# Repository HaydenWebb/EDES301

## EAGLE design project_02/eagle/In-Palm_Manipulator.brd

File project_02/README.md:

# In-Palm 2DoF Manipulator PCB
Implementation files (gerber, schematic, BOM, etc.) for generating a PCB for the manipulator

## Project Description
In-the-palm 2DoF manipulator that will be worn on both the forearm and hand. This device will be comprised of an active surface (i.e. a pulley belt) and turntable that will be actuated by two micro DC motors. The control of this device will be actuated by four pressure sensors that will be inlaid along the wrist to measure the bend of the wrist. Depending on the bend of the wrist, either the turntable or active surface will turn on and move.

## PCB Description
The components for this board is a PocketBeagle, L293D, and MT3608. They are connected together through a 4-layer, copper board and has 5mm mounting brackets inset in the corners.

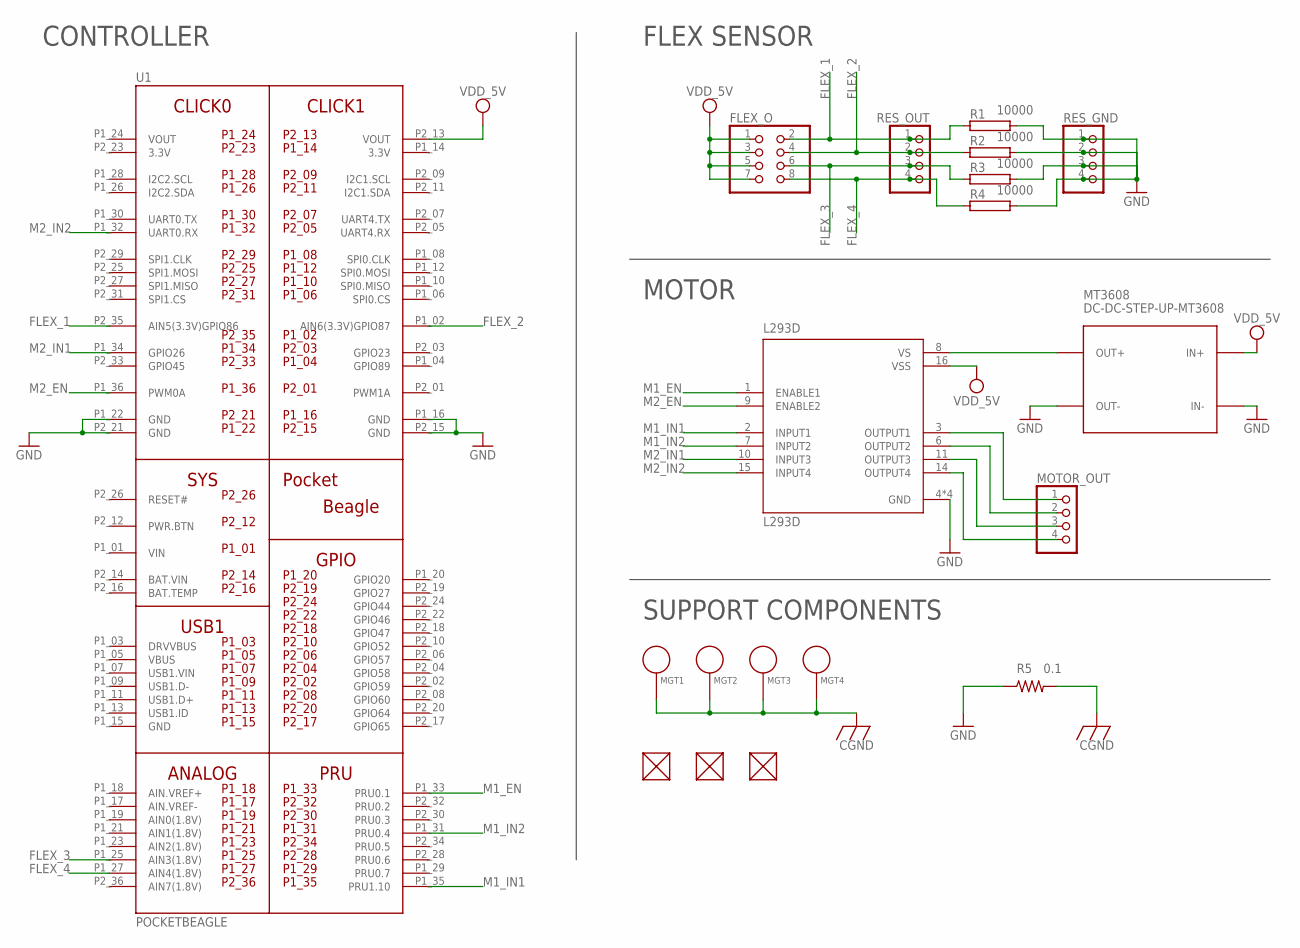
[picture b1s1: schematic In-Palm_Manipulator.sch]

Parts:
FLEX_O: PINHD-2X4; 2X04
FUD1, FUD2, FUD3: FIDUCIAL; FIDUCIAL_40MIL
L293D: L293D; DIP880W50P254L2000H510Q16
MGT1, MGT2, MGT3, MGT4: MOUNTING_HOLE
MOTOR_OUT: PINHD-1X4; 1X04
MT3608: DC-DC-STEP-UP-MT3608
R1, R2, R3, R4: 10000; HPS58
R5: 0.1; R0603
RES_GND: PINHD-1X4; 1X04
RES_OUT: PINHD-1X4; 1X04
U1: POCKETBEAGLE

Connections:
3.3V: U1.P1_14 (3.3V), U1.P2_23 (3.3V)
BAT.VIN: U1.P2_14 (BAT.VIN)
CGND: MGT1.P$1, MGT2.P$1, MGT3.P$1, MGT4.P$1, R5.2
FLEX_1: FLEX_O.2, R1.1, RES_OUT.1, U1.P2_35 (AIN5(3.3V)GPIO86)
FLEX_2: FLEX_O.4, R2.1, RES_OUT.2, U1.P1_02 (AIN6(3.3V)GPIO87)
FLEX_3: FLEX_O.6, R3.1, RES_OUT.3, U1.P1_25 (AIN3(1.8V))
FLEX_4: FLEX_O.8, R4.1, RES_OUT.4, U1.P1_27 (AIN4(1.8V))
GND: L293D.4 (GND), L293D.5 (GND), L293D.12 (GND), L293D.13 (GND), MT3608.IN-, MT3608.OUT-, R1.2, R2.2, R3.2, R4.2, R5.1, RES_GND.1, RES_GND.2, RES_GND.3, RES_GND.4, U1.P1_16 (GND), U1.P1_22 (GND), U1.P2_15 (GND), U1.P2_21 (GND)
M1_EN: L293D.1 (ENABLE1), U1.P1_33 (PRU0.1)
M1_IN1: L293D.2 (INPUT1), U1.P1_35 (PRU1.10)
M1_IN2: L293D.7 (INPUT2), U1.P1_31 (PRU0.4)
M2_EN: L293D.9 (ENABLE2), U1.P1_36 (PWM0A)
M2_IN1: L293D.10 (INPUT3), U1.P1_34 (GPIO26)
M2_IN2: L293D.15 (INPUT4), U1.P1_32 (UART0.RX)
unnamed: L293D.8 (VS), MT3608.OUT+
unnamed: L293D.3 (OUTPUT1), MOTOR_OUT.1
unnamed: L293D.6 (OUTPUT2), MOTOR_OUT.2
unnamed: L293D.11 (OUTPUT3), MOTOR_OUT.3
unnamed: L293D.14 (OUTPUT4), MOTOR_OUT.4
VDD_5V: FLEX_O.1, FLEX_O.3, FLEX_O.5, FLEX_O.7, L293D.16 (VSS), MT3608.IN+, U1.P2_13 (VOUT)
VIN: U1.P1_01 (VIN)
VOUT: U1.P1_24 (VOUT)

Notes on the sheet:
FLEX SENSOR
MOTOR
CONTROLLER
SUPPORT COMPONENTS

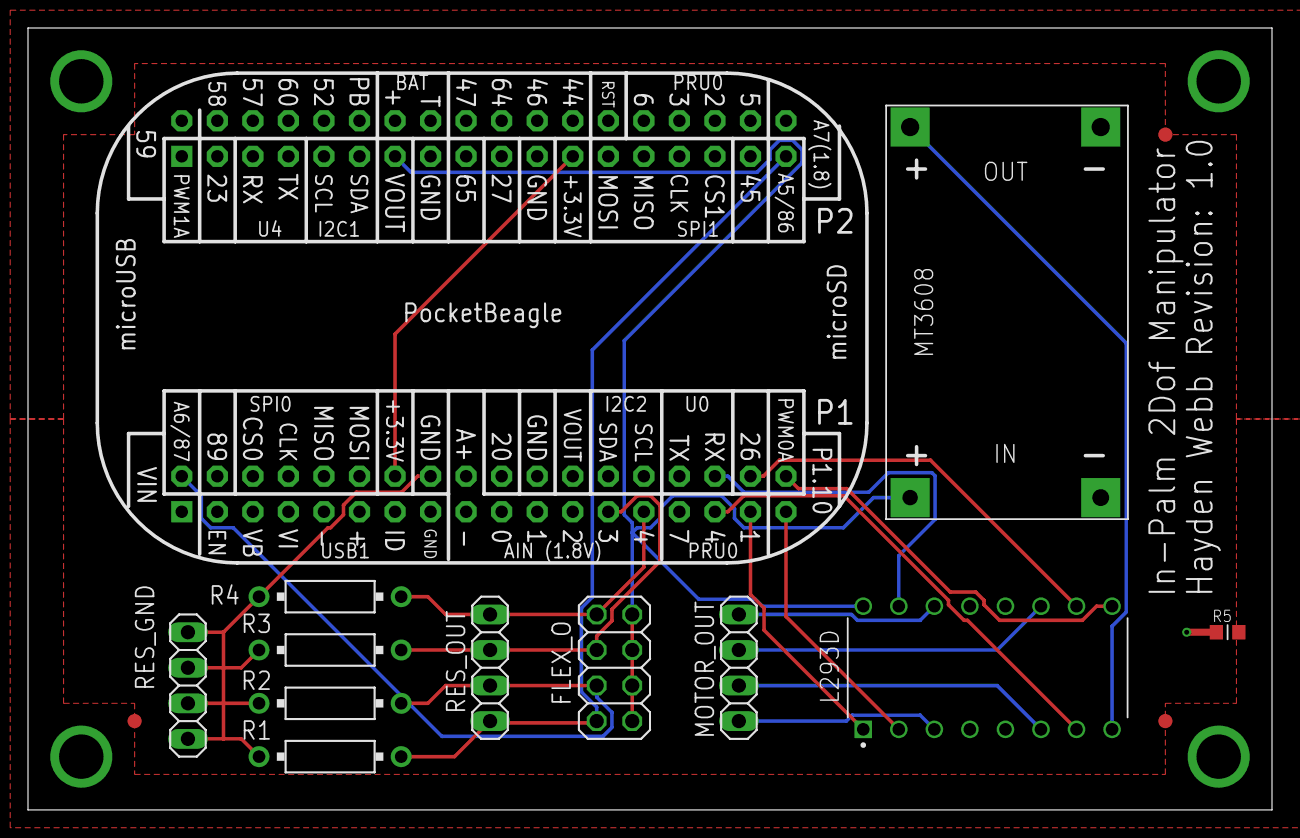
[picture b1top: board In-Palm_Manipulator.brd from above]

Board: 4 copper layers, 88.9 x 55.9 mm, 19 parts (0 on the bottom side), 19 nets.

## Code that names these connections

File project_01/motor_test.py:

#!/usr/bin/env python3
import os
import time
import Adafruit_BBIO.GPIO as GPIO
import Adafruit_BBIO.PWM  as PWM

M2_EN,  M2_IN1,  M2_IN2 = "P1_33", "P1_35", "P1_31"
M1_EN,  M1_IN1,  M1_IN2 = "P1_36", "P1_34", "P1_32"

os.system(f"config-pin {M1_EN} pwm")
os.system(f"config-pin {M2_EN} pwm")
for pin in (M1_IN1, M1_IN2, M2_IN1, M2_IN2):
    os.system(f"config-pin {pin} gpio")
    GPIO.setup(pin, GPIO.OUT)

PWM.start(M1_EN, 0, 1000)   # 1 kHz, 0% duty (off)
PWM.start(M2_EN, 0, 1000)

def motor_on(en, in1, in2, speed_pct=100):
    """Run motor in CW or CCW at speed_pct%."""
    GPIO.output(in1, GPIO.HIGH)
    GPIO.output(in2, GPIO.LOW)
    PWM.set_duty_cycle(en, speed_pct)


def motor_off(en, in1, in2, coast=True):
    """Stop motor; if coast=False, actively brake."""
    PWM.set_duty_cycle(en, 0)
    if not coast:
        # active brake: tie both inputs together
        GPIO.output(in1, GPIO.HIGH)
        GPIO.output(in2, GPIO.HIGH)

if __name__ == "__main__":
    print("Starting alternating motor test (Ctrl-C to quit)...")
    try:
        while True:
            print("→ MOTOR 1 ON")
            try:
                motor_on(M1_EN, M1_IN1, M1_IN2)
            except Exception as e:
                print("Error in motor_on(M1):", repr(e))
            time.sleep(2.0)

            print("→ MOTOR 1 OFF (coast)")
            try:
                motor_off(M1_EN, M1_IN1, M1_IN2, coast=True)
            except Exception as e:
                print("Error in motor_off(M2):", repr(e))
            time.sleep(2.0)

            print("→ MOTOR 2 ON (coast)")
            try:
                motor_on(M2_EN, M2_IN1, M2_IN2, coast=True)
            except Exception as e:
                print("Error in motor_off(M1):", repr(e))
            time.sleep(0.5)

            print("→ MOTOR 2 OFF")
            try:
                motor_off(M2_EN, M2_IN1, M2_IN2)
            except Exception as e:
                print("Error in motor_on(M2):", repr(e))
            time.sleep(2)

    except KeyboardInterrupt:
        print("\nInterrupted; shutting down motors and cleaning up.")
        # Ensure motors are off
        motor_off(M1_EN, M1_IN1, M1_IN2)
        motor_off(M2_EN, M2_IN1, M2_IN2)
        # Stop and cleanup PWM/GPIO
        PWM.stop(M1_EN)
        PWM.stop(M2_EN)
        PWM.cleanup()
        GPIO.cleanup()
        print("Done.")

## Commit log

2025-02-02 HW2 Q3
2025-02-18 Added assignment_03 and simple_calc
2025-02-18 Finished Q1
2025-02-18 Finished Q2
2025-02-18 Finished HW4 Q4
2025-02-23 Project_01 Entry
2025-03-08 Software Proposal
2025-04-30 Project_01 (Forgot to push from Beagle)
2025-04-30 Fixed Link for Hackster
2025-05-05 Project_02
